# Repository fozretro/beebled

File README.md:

BeebLED
=======

So after nearly a year at this point (24th Nov 2022) of learning electronics, "re"collecting various retro computers, modifying and fixing them. I figured I would revist a childhood dream to have my own scrolling message board! Just like the ones down my local kebab shop! So lets build an LED matrix scroller for the Beeb! The proof of concept can be found [here](https://www.reddit.com/r/beneater/comments/xq2d4h/completed_6502_project_with_led_scroller/).

You can also see a demo video [here](https://drive.google.com/file/d/1L_YhwlXpUD0SaMJsGKrx3CFpbm8zI_nu/view).

Credits
=======
- [Ben Eater](https://eater.net/6502), for opening my eyes to the joy of hardware and software building together!
- [Anders Brauner Nielsen](https://abnielsen.com), his well timed [blog](https://abnielsen.com/2021/12/23/ws2812b-rgb-lights-on-a-6502/) turned up (to my suprise) in my web searches for 6502 and LEDs! His ingenious circuit, with some additional components and modificaitons is at the core of this solution! Thank you Anders!
- [StarDot Forums](https://stardot.org.uk/forums/), the place for advice and encourgement for all your Acorn projects! This project uses [BeebASM](https://github.com/stardot/beebasm), [UPURSFS](https://www.retro-kit.co.uk/UPURS/) and [Visual Studio Code Extension for BeebASM](https://marketplace.visualstudio.com/items?itemName=simondotm.beeb-vsc). The authors of these amazing tools also hangout on stardot!

Usage
=====

It is a little early in development to complete this section, though my eventual goal is some kind of ROM, possibly using sideways RAM to avoid using the main RAM. Maybe even a VDU driver to plot stuff on the LED display? For now please see [this StarDot Forum thread](https://stardot.org.uk/forums/viewtopic.php?f=3&t=26047).

Developmet Tools
================

The ```/dist``` always contains the latest .ssd, but if you want to try to build it locally this section contains my notes on how I set things up with UPURSFS.

- Shift+Command+B bulds stuff and copies over to ```/dev/beebled``` and ```/dist```
- Shift+Ctrl+T launches the emulator (hard coded to where I have it)
- See below for connecting Beeb to the ```/dev/beebled``` folder to test hardware

Running UPURSFS and TubeHost
----------------------------

This enables the fastest possible inner loop for development, build on the Mac and instantly the compiled output is visble to the connected Beeb! This is especially useful since the only way (currently without mocking) is to see results is on real hardware.

**On the Beeb**, have UPURSFS ROM installed and pressing U+Break, U+Crl+Break or U+Shift+Break. If it says (No RTS) things are not connected - check the cable. See general instructions in the ```/bin/UPURSFS/Tubehost/README.txt```. ```*HSTATUS``` is a good test command. Press Ctrl+U+Break to boot the ```/dev/beebled``` disc on the Beeb. Note if you have ```Configure BOOT``` setup you have to use Ctrl+U+Break, if this gets frustrating just switch auto boot off.

**On the Mac**, you need to run ```/bin/UPURSFS/TubeHost/TubeHost.perl```. I had some issues running it and posted on StarDot forums what I found and my fix, see [here](https://stardot.org.uk/forums/viewtopic.php?f=3&t=24976) and also other tips.

```perl ./bin/UPURSFS/TubeHost/TubeHost.perl -U /dev/cu.usbserial-FTCL544Z```

By default the files it serves up to the BBC are in ```$HOME/Beeb_Disks```, however the above script has been modified to serve from ```/dev```. Note that when working on the files on the Beeb changes are also instantly reflected as well. For example when editing the sprites using the native Acorn GFX sprite editor and commands as described below.

Updating Sprites
----------------

Sprites can be used in the scroller and use the Acorn GFX sprite file format. You must then use the Acorn GFX Sprites ROM if on Master (as shown below), or one of the others if on other systems to edit. Note if you use a Master to edit the sprites and use the ROM in Sideways RAM the reminder of the ram bank is used for your sprites storage nice! Bellow is using indirect way of loading via memory as on UPURS ```SRLOAD``` command hangs.

```*LOAD R.SPRITES 3000```

```*SRWRITE 3000 6000 8000 4```

```*SLOAD Sprites```

Use commands like ...

```*SEDIT 1```

```*SDELETE 1```

```*SRENUMBER 4 1```

Then use to save ... (last two commands if on UPURS only)

```*SSAVE Sprites```

```*HTSTATUS```

```*CLOSE```

TODO's
======

Software
--------
- Add support #s command to support sprites of different heights (hard coded to 8)
- Build config. for the MODE2 emulation of LED output (consider using MODE 8)
- Remove hard coded mode2 calculated rows table and replace with asm macro script?
- Add config to support different size led panels, constants and logic behavior hard codedto 11x44
- It is not optimized other than having a secondary display buffer to ensure consistent timing output to the LED. Likely when I share this further, it can be optimized even further with feedback. 
- Implement 1 pixel scroll (currently 2 pixel)
- Eventually I would like to have the code in a ROM, e.g. *BEEBLED Hello World, or *BEEBLED #m3000 (displays whats on screen), and/or maybe a VDU driver? Not sure what to do about storage, use sideways ram if ROM loaded into sideways ram bank? Otherwise take PAGE?

Hardware
---------
- Experiment with adding additional 11x44 pixel matrix for longer and/or wider displays

Development Diary
=================

26th May 2023
-------------
- Made some fixes to the schematic and PCB design
- 1/ flipped diode around
- 2/ removed pcb JST connector (could not find one for JST SM based connectors) and replaced with pin headers and annotated 
- 3/ increased footprint size of 1000uF capacitor 
- 4/ added a little more labelling on the pcb
- 5/ updated to v1.2
- I kinda like it without a case and don't have the skills or hardware to design one (nor time, space, $ to invest at this point in that hobby)
- So I am thinking once the hardware design is stable I will turn full attention to the software TODO's above
- Next step is to double check above changes and send off for a new PCB, build it and test it

20th May 2023
-------------
- Week prior to today, the PCB arrived from PCBWay, along with various components
- Assemebling on and off during weekday evenings
- First test failed!
- Made a quick hack to the code to simply flip 1 LED off and on with a keypress, should add this in the future as a flag
- After compariing with the prototype and studying the PCB layout, realized i flipped the diode footprint on the PCB layout!
- Also found that the matrix JST connector I used is to small
- Have the breadboard prototype to compare signals really helped!
- After a soldering the matrix fly lead diretly to the PCB for now, and flipping the diode, success!
- Next job fix the PCB design, and source larger JST connector, also publish a BOM
- Then build the next version!

5th May 2023
------------
- Reproduce the circuit in Kicad
- Design the PCB in Kicad
- Build PCB via PCBWay
- Share the designs

Dec 25th
--------
- Removed hard coded font and used OS API to get character definitions

Dec 24th
--------
- Updated flash screen with new BeebLED logo
- Shorter default message with new holiday themed sprite!
- Published repo on fozretro GitHub
- Made a video shared on StarDot

Dec 21-23rd
-----------
- Implemented expressing sprite, text color changes and pause in message string

```#cX - Text color where x is 0-7```

```#pX - Pause for 0-9 seconds```

```#sX - Scroll on sprite 0-9 for now assumed 8 pixels with, but can be variable width```

```#dX - Display sprite 0-9 then scroll```

- Acorn GFX sprites are stored in logical top-down order for rows but right-left order horizontally, would love to know why?!?! Optimization in the sprite plotting code?

Dec 20th
--------
- Fixed the colors on the LED since moving to how true Mode 2 pixels are encoded
- Its not the most performant code right now - more tables or something needed in the future
- Refactored a little into two other .asm files
- Added some commands as follows

```#cX - Text color where x is 0 to 7```

```#sp - Pause for 0 to 9 seconds```

```#d - Display sprite 0```

Dec 19th
--------
- Broke the pixel coloring being output to the LED, since using true Mode 2 pixel encoding
- Removed hard coded scrolling message and splash screen
- Now loads from Acorn GFX sprite file and text file respectively
- Very strange format for sprites not sure how performant it will be to scroll in sprites
- Oh and implemented a debug feature to write to mode 2 screen as well as the LED
- Made sure all files under ```/dev/beebled``` are also copied to ```.ssd```

Dec 18th
--------
- In understanding the Acorn GFX sprite editor I mostly spent a few hours realizing my encoding for MODE 2 I had in mind was wrong and does not match the Beebs after all!
- So I wanted some way to easily add graphics into the scroller and decided to investigate the Acorn GFX sprite editor and its file format ... (later read same on StarDot doh)
    - File length - 2 bytes (including these two bytes)
    - Number of spirtes in file (not zero based) - 1 byte
    - Sprite
        - width (in bytes - base zero) - 1 byte
        - height (in bytes - base zero) - 1 byte
        - size (in bytes) - 2 byte
        - mode - 1 byte
        - id - 1 byte
        - data - bytes
- Ideas for message text format and making BeebLED configurable!
    - Scroll on a sprite, sprites smaller than 11 pixels in height get a border
    - Option to just display it a sprite on a clear screen then scroll
    - Scroll text uses built in font (for now!)
    - Pause the scrolling for x seconds
    - Change scroll direction 
    - Syntax ideas... ```#S1 #P5 This is the rest of the message... I #S2 my Beeb!```
    - Have sprites dynamically loaded, if ```Sprites``` file exists
    - Have message dynanically loaded, if ```Message``` file exists
- Added GFX ROMS and setup dummy config files Sprites and Message
- Drew the very early prototype splash screen from Sarah and stores in ```Sprites```

Dec 16th
--------
- Added basic argument reading to pass in different messages (really just to play with it for now - want to make a set of ROM commands for this). Now supports ```*BEEBLED My Message!```
- Exit the app on key press back to command line

Dec 12th
--------
- Fixed most of the gitter I  was seeing by remove fly leds, attach end of cable direct to breadboard - it still occurs now and again - but not enough to stop me progressing with some more of the software side of things

Dec 11th
--------
- Ported over code from my Ben Eater project which used a different compiler and memory addreses.
- Success! We have LED scroller powered by a BBC Micro!
- Well with the some glitching, which I think is due to fly leads etc. So I think I will atttempt to direct connect the User Port cable end more directly to the board with some pins.
- This is quite a milestone, so once I can fix the glitching I'll do a share on stardot
- Next up make the software a bit more accessible, to pass a message in from the command line
- After that likely I can split my time between software and progressing a schematic and pcb

Dec 10th
---------
- After much reading and re-learning I probed each of the steps in converting the Beebs clock pulse into a pulse to latch the data into the serial output IC. I noticed the inversion happening and decided to use an additional input/output on the 74HC14, 6A and 6Y, to have pulse generated on the actual Beebs pulse, not the inversion of it.
- I also found that if I have the LEDs to bright, the signal I think suffers and LEDs remain on or don't show the correct color. I probably need some more smoothing capactitors in some place?!?! Anyway the software fix was to low the brightness and hey presto it all stablized! I fill the 11x44 matrix with pixels and toggled them on and off with success. 
- Next up more fun with software for a bit! Scrolling message here we come!

Dec 4th
-------
- WIP > Coping over some code from my very first prototype [here](https://www.reddit.com/r/beneater/comments/wd6irw/ben_eater_6502_computer_driving_ws2812b_rgb_leds/) - trigger based on keypress as no timer code setup yet
- Partial success I can toggle an LED and show a strip of them..... but the signals are out
- However on closer inspection the data signal to LED matrix is missing the first bit of each byte sent via CB2, it sends a 0 and then only the first 7 bits from CB2 are being sent. Looking at it through my scope I can see that the small pulse sent to the PL pin is being sent to soon before data on CB2 starts to be sent. Afterwards due to timing the second pulse picks up the tail end of the first bit of data from CB2, but by this time the circuit has of course sent 1 of 8 bits.
-When I look at the data sheet for mode 110 it does show this as well. The odd thing is on the Ben Eater system above it worked fine (I plan to do more compares at the weekend with my scope).

Dec 2nd, 3rd
--------
- Built a new breadboard of the circuit to send to LED matrix I used for my Ben Eater computer [here](https://www.reddit.com/r/beneater/comments/wd6irw/ben_eater_6502_computer_driving_ws2812b_rgb_leds/)
- Tested on the above and works fine - yay!
- Will it work on the Beeb though? Is the data line to long? Had sights of clitchs on the original breadboard when this was the case?

27th Nov
--------
- Labelled up some GND, CB1 and CB2 fly leads from the cable socket ready to plug into breadboard
- Write some basic code that sets up the VIA and send bytes (keyboard input)so I could monitor with my scope to check the basic serial output is working from beeb user port. Monitoring CB1 and CB2 shows signals as expected. Nice!
- Also fixed !BOOT

26th Nov
--------
- Udpated the README with some info on the dev tools and captured pinout for user port
- Some good notes [here](https://stardot.org.uk/forums/viewtopic.php?t=11671) on testing user port
- I tested my cable pins do have 5v on them yay!

24th Nov
--------
- Built a BBC user port cable and tested continuity it with my meter
- Setup this project with various VSCode tasks and levergaging the UPURSFS file system to make stuff available instantly on the connected Beeb for testing.

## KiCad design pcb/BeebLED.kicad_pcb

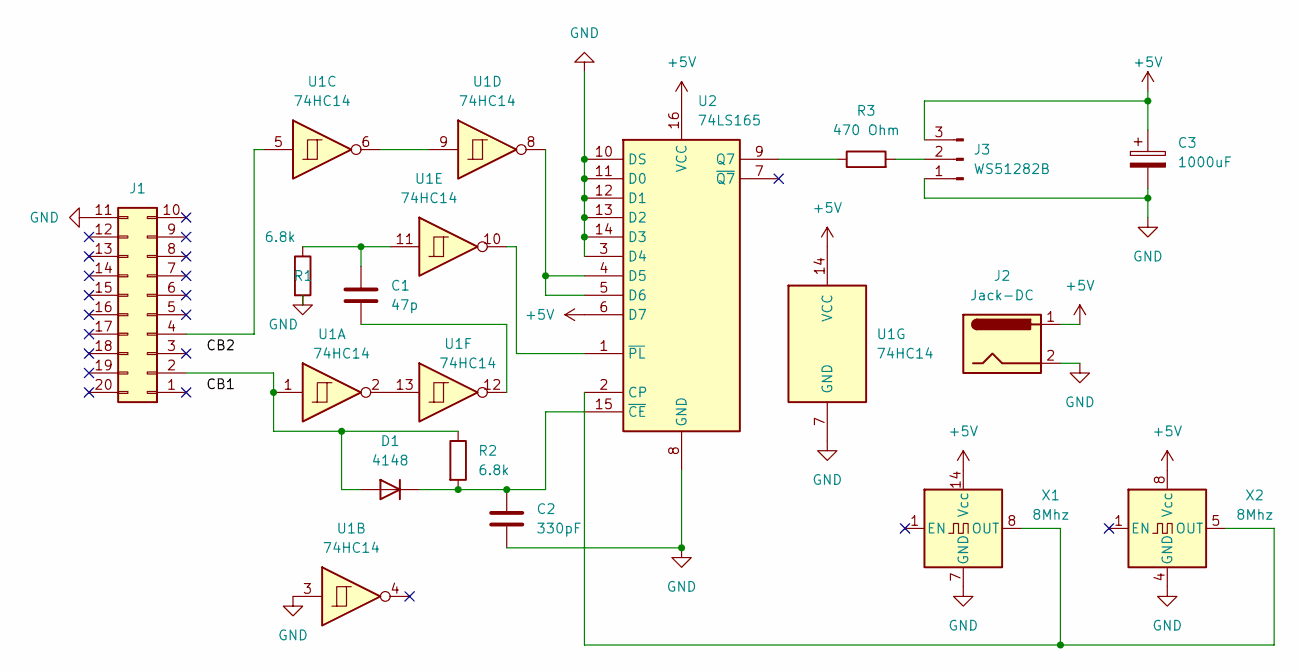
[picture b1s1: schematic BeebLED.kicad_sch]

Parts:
C1: 47p; C_Disc_D5.0mm_W2.5mm_P2.50mm
C2: 330pF; C_Disc_D5.0mm_W2.5mm_P2.50mm
C3: 1000uF; CP_Radial_D10.0mm_P5.00mm
D1: 4148; D_A-405_P7.62mm_Horizontal
J1: IDC-Header_2x10_P2.54mm_Horizontal
J2: Jack-DC; BarrelJack_CUI_PJ-063AH_Horizontal_CircularHoles
J3: WS51282B; PinHeader_1x03_P2.54mm_Vertical
R1, R2: 6.8k; R_Axial_DIN0207_L6.3mm_D2.5mm_P10.16mm_Horizontal
R3: 470 Ohm; R_Axial_DIN0207_L6.3mm_D2.5mm_P10.16mm_Horizontal
U1: 74HC14; DIP-14_W7.62mm_Socket
U2: 74LS165; DIP-16_W7.62mm_Socket
X1: 8Mhz; Oscillator_DIP-14
X2: 8Mhz; Oscillator_DIP-8

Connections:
+5V: C3.1, J2.1, J3.3, U1.14 (VCC), U2.6 (D7), U2.16 (VCC), X1.14 (Vcc), X2.8 (Vcc)
GND: C2.2, C3.2, J1.11, J2.2, J3.1, R1.2, U1.3, U1.7 (GND), U2.3 (D4), U2.8 (GND), U2.10 (DS), U2.11 (D0), U2.12 (D1), U2.13 (D2), U2.14 (D3), X1.7 (GND), X2.4 (GND)
unnamed: C1.1, R1.1, U1.11
unnamed: C1.2, U1.12
unnamed: C2.1, D1.2 (K), R2.2, U2.15 (~CE)
unnamed: D1.1 (A), J1.2, R2.1, U1.1
unnamed: J1.4, U1.5
unnamed: J3.2, R3.2
unnamed: R3.1, U2.9 (Q7)
unnamed: U1.6, U1.9
unnamed: U1.8, U2.4 (D5), U2.5 (D6)
unnamed: U1.10, U2.1 (~PL)
unnamed: U1.2, U1.13
unnamed: U2.2 (CP), X1.8 (OUT), X2.5 (OUT)

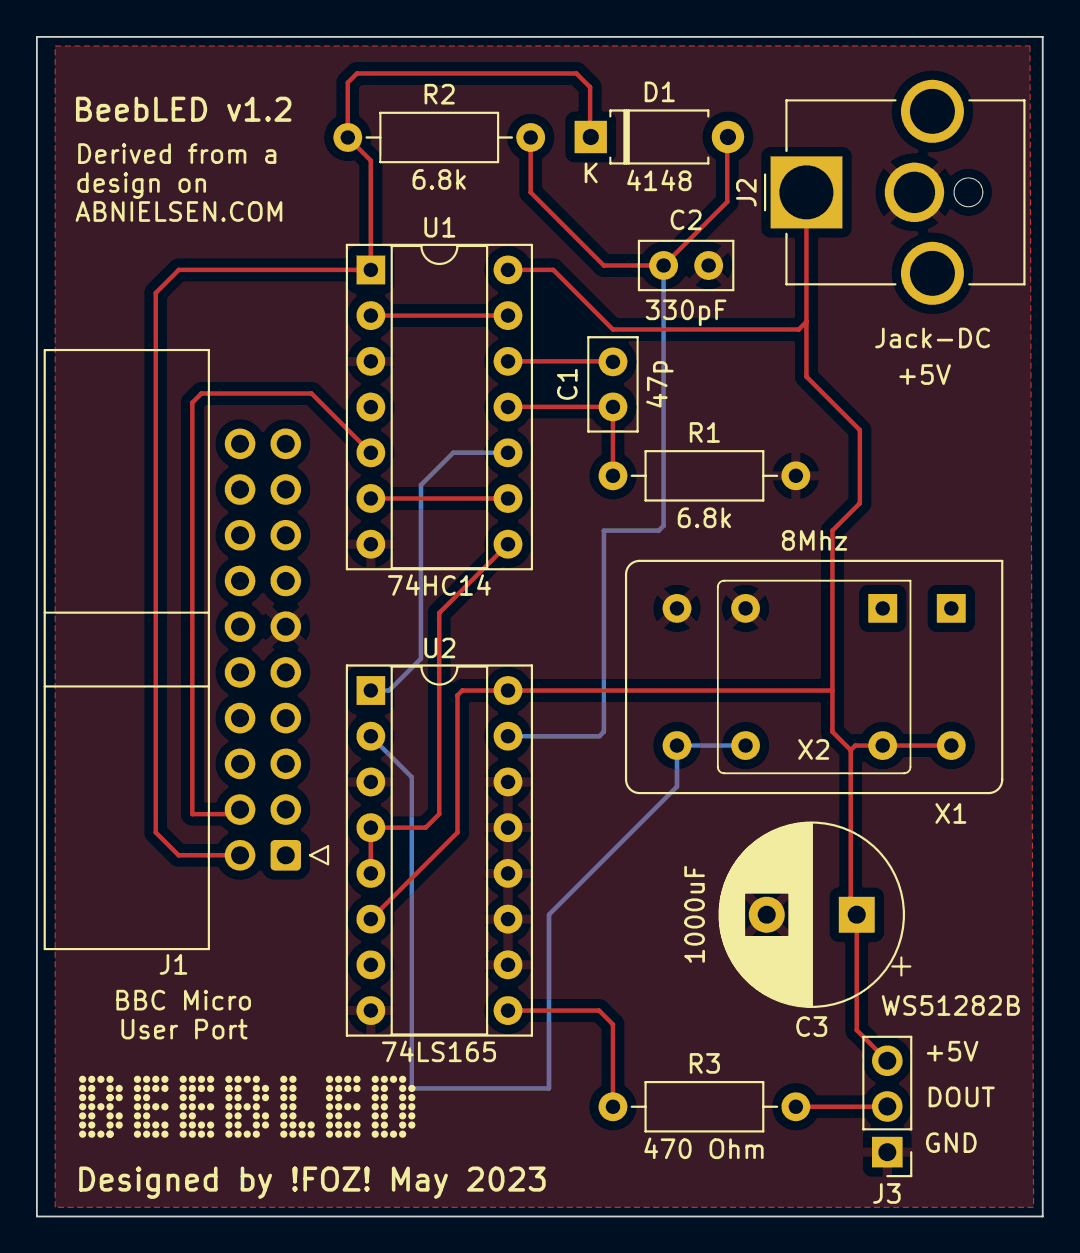
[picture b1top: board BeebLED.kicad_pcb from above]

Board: 2 copper layers, 55.9 x 65.5 mm, 14 parts (0 on the bottom side), 14 nets.

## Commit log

2022-12-25 Replaced hard coded font with calls to OS to get chardef
    Users can also now customize the font and add special characters via traditional means prior to calling BeebLED
2023-05-05 Added schematic and pcb
2023-05-05 Fixed 8 Mhz not connected
2023-05-06 Changed J3 connector type and tied U1 Pin 3 to GND
    Thanks to the advice from stardot! :-)
2023-05-06 Added support for DIP8 crystal
2023-05-07 Added alternative X2 component to schema and updated PCB
2023-05-07 Added a logo
2023-05-07 Generated gerber files
2023-05-21 Updated readme and new images
    Updated readme and new images
2023-05-26 Updated to v1.2 schematic and pcb design
    Requires further testing
2023-05-27 Updated fabrication files
